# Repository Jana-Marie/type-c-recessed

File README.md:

# type-c-recessed

My simple solution of bringing USB Type-C power receptacles flush into circuit boards, thus allowing for beautiful faceplates and PCB based user interfaces.

<table>
  <tbody>
    <tr>
      <td>
        
      </td>
      <td>
        
      </td>
    </tr>
    <tr>
      <td>
        
      </td>
      <td>
        
      </td>
    </tr>
  </tbody>
</table>

## notes

If you want to use this solution, please get the designfiles in the 'hardware files/' folder produced, add a 6-Pin USB-C power only connector and two 5.1k 1% resistors to each board. If neccessary, please also add a 4.7uF cap to the back of each board.

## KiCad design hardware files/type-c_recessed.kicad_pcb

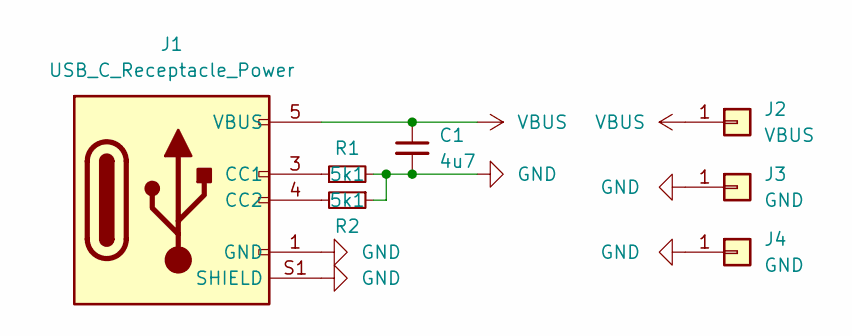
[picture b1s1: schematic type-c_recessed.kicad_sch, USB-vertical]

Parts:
C1: 4u7; C_0805
J1: USB_C_Receptacle_Power; USB-C_Power
J2: VBUS; pad_1_2
J3, J4: GND; pad_1_2
R1, R2: 5k1; R_0402

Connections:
GND: C1.2, J1.1 (GND), J1.6 (GND), J1.S1 (SHIELD), J3.1, J4.1, R1.2, R2.1
unnamed: J1.3 (CC1), R1.1
unnamed: J1.4 (CC2), R2.2
VBUS: C1.1, J1.2 (VBUS), J1.5 (VBUS), J2.1

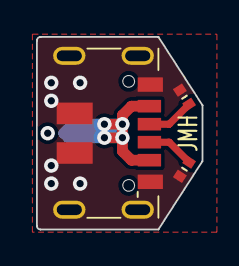
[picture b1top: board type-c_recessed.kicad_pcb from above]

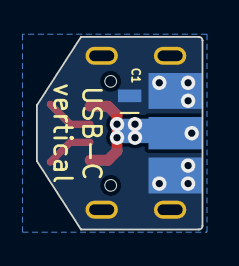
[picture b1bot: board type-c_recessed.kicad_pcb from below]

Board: 2 copper layers, 9.2 x 10.7 mm, 7 parts (4 on the bottom side), 4 nets.

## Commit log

2024-05-28 added gitignore
2024-05-28 added footprint
2024-05-28 added stepfile
2024-05-28 added hardware files
2024-05-28 added license
2024-05-28 swapped readme images
